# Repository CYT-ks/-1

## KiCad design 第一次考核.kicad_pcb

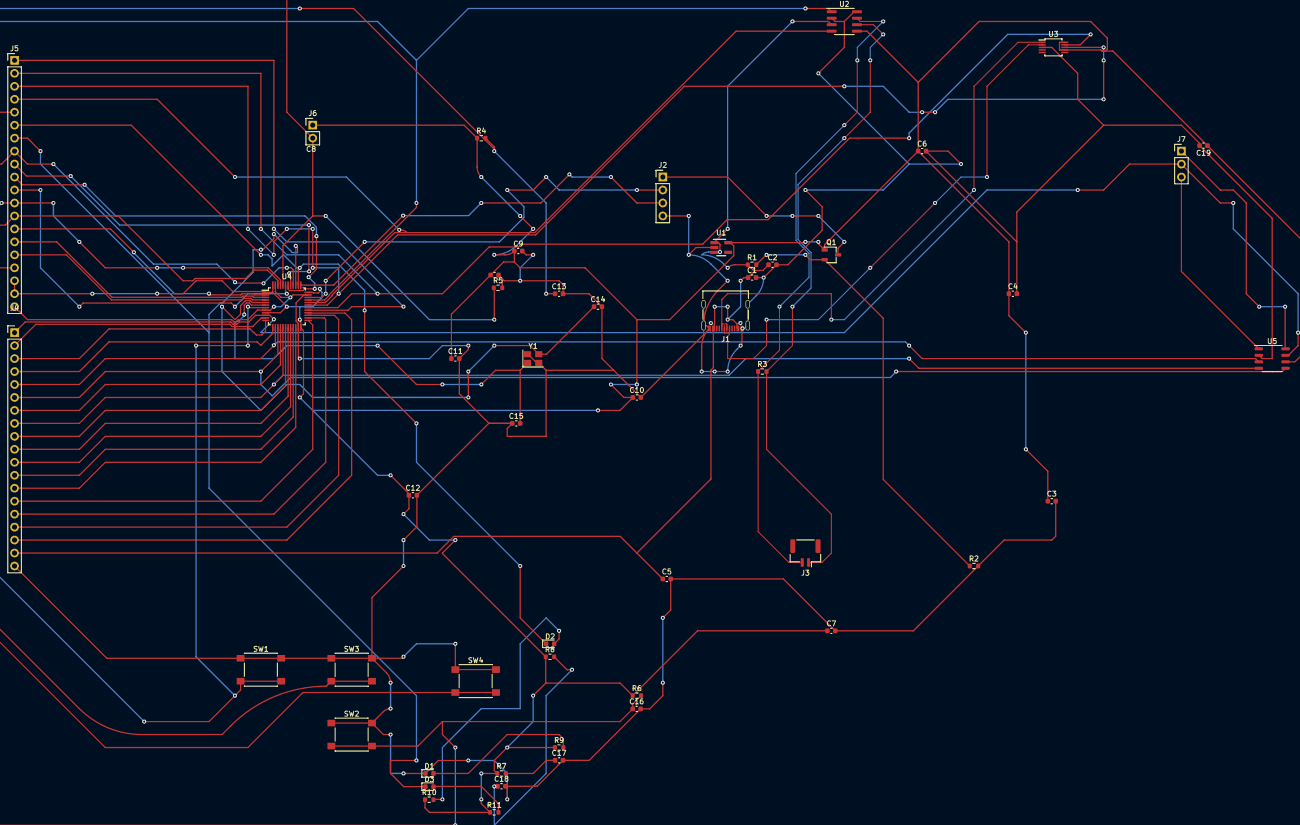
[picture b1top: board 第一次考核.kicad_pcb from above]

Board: 2 copper layers, 51 parts (0 on the bottom side), 55 nets.

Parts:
C1, C3: 10u; C_0603_1608Metric
C2, C4, C5, C6, C7, C8, C9, C10, C11, C12, C13, C16, C17, C18, C19: 100n; C_0603_1608Metric
C14, C15: 18p; C_0603_1608Metric
D1, D2, D3: LED; LED_0603_1608Metric
J1: USB_C_Receptacle_USB2.0; USB_C_Receptacle_Palconn_UTC16-G
J2: PinHeader_1x04_P2.54mm_Vertical
J3: Conn_01x02; JST_GH_SM02B-GHS-TB_1x02-1MP_P1.25mm_Horizontal
J4: Conn_01x19; PinHeader_1x19_P2.54mm_Vertical
J5: Conn_01x20; PinHeader_1x20_P2.54mm_Vertical
J6: Conn_01x02; PinHeader_1x02_P2.54mm_Vertical
J7: Conn_01x03; PinHeader_1x03_P2.54mm_Vertical
Q1: TSOT-23
R1: 1k; R_0603_1608Metric
R2, R4, R5: 10k; R_0603_1608Metric
R3: 120; R_0603_1608Metric
R6, R7, R8: 1K; R_0603_1608Metric
R9, R10, R11: R; R_0603_1608Metric
SW1, SW2, SW3, SW4: SW_Push; SW_Push_1P1T_NO_6x6mm_H9.5mm
U1: HX9193; SOT-23-5_HandSoldering
U2: TJA1051T-3; SOIC-8_3.9x4.9mm_P1.27mm
U3: CH340E; MSOP-10_3x3mm_P0.5mm
U4: STM32F103C8T6; LQFP-48_7x7mm_P0.5mm
U5: AD8400ARZ50; SOP-8_3.9x4.9mm_P1.27mm
Y1: 12M; Crystal_SMD_3225-4Pin_3.2x2.5mm

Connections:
+3V3: C3.1, C4.1, C6.1, C7.1, C8.1, C9.1, C10.1, C11.1, C12.1, C19.1, J5.18, J5.19, J6.1, Q1.1 (D), R4.1, R6.1, R7.1, R8.1, R9.1, R10.1, R11.1, U1.5 (VOUT), U2.5 (VIO), U3.7 (VCC), U3.10 (V3), U4.1 (VBAT), U4.9 (VDDA), U4.24 (VDD), U4.36 (VDD), U4.48 (VDD), U5.6 (VDD)
/PORT&POWER/3V3_Debug: J2.1, Q1.3 (S)
/PORT&POWER/CAN+: J3.2, R3.1, U2.7 (CANH)
/PORT&POWER/CAN-: J3.1, R3.2, U2.6 (CANL)
/PORT&POWER/D+: J1.A6 (D+), J1.B6 (D+), U3.1 (UD+)
/PORT&POWER/D-: J1.A7 (D-), J1.B7 (D-), U3.2 (UD-)
/STM32_MinimumSystem/BOOTO: J5.17, J6.2, R5.1, U4.44 (BOOT0)
/STM32_MinimumSystem/NRST: C13.1, R4.2, SW1.2, U4.7 (NRST)
/STM32_MinimumSystem/OSC_IN: C14.1, U4.5 (PD0), Y1.3
/STM32_MinimumSystem/OSC_OUT: C15.2, U4.6 (PD1), Y1.1
/STM32_MinimumSystem/PA0: J4.1, J7.2, U4.10 (PA0), U5.7 (W1)
/STM32_MinimumSystem/PA1: J4.2, U4.11 (PA1)
/STM32_MinimumSystem/PA2: J4.3, U4.12 (PA2)
/STM32_MinimumSystem/PA3: J4.4, U4.13 (PA3)
/STM32_MinimumSystem/PA4: J4.5, U4.14 (PA4), U5.3 (~CS)
/STM32_MinimumSystem/PA5: J4.6, U4.15 (PA5), U5.5 (CLK)
/STM32_MinimumSystem/PA6: J4.7, U4.16 (PA6)
/STM32_MinimumSystem/PA7: J4.8, U4.17 (PA7), U5.4 (SDI)
/STM32_MinimumSystem/PA8: J5.1, U4.29 (PA8)
/STM32_MinimumSystem/PA9: J5.2, U3.9 (RXD), U4.30 (PA9)
/STM32_MinimumSystem/PA10: J5.3, U3.8 (TXD), U4.31 (PA10)
/STM32_MinimumSystem/PA11: J5.4, U2.4 (RXD), U4.32 (PA11)
/STM32_MinimumSystem/PA12: J5.5, U2.1 (TXD), U4.33 (PA12)
/STM32_MinimumSystem/PA13: J2.2, U4.34 (PA13)
/STM32_MinimumSystem/PA14: J2.3, U4.37 (PA14)
/STM32_MinimumSystem/PA15: D2.1 (K), J5.6, U4.38 (PA15)
/STM32_MinimumSystem/PB0: J4.9, U4.18 (PB0)
/STM32_MinimumSystem/PB1: J4.10, U4.19 (PB1)
/STM32_MinimumSystem/PB2: J4.11, U4.20 (PB2)
/STM32_MinimumSystem/PB3: D3.1 (K), J5.7, U4.39 (PB3)
/STM32_MinimumSystem/PB4: C16.1, J5.8, R6.2, SW2.2, U4.40 (PB4)
/STM32_MinimumSystem/PB5: J5.9, U4.41 (PB5)
/STM32_MinimumSystem/PB6: J5.10, U4.42 (PB6)
/STM32_MinimumSystem/PB7: J5.11, U4.43 (PB7)
/STM32_MinimumSystem/PB8: J5.12, SW3.2, U4.45 (PB8)
/STM32_MinimumSystem/PB9: J5.13, SW4.2, U4.46 (PB9)
/STM32_MinimumSystem/PB10: J4.12, U4.21 (PB10)
/STM32_MinimumSystem/PB11: J4.13, U4.22 (PB11)
/STM32_MinimumSystem/PB12: J4.14, U4.25 (PB12)
/STM32_MinimumSystem/PB13: J4.15, U4.26 (PB13)
/STM32_MinimumSystem/PB14: J4.16, U4.27 (PB14)
/STM32_MinimumSystem/PB15: J4.17, U4.28 (PB15)
/STM32_MinimumSystem/PC13: J5.14, U4.2 (PC13)
/STM32_MinimumSystem/PC14: J5.15, U4.3 (PC14)
/STM32_MinimumSystem/PC15: J5.16, U4.4 (PC15)
GND: C1.2, C2.2, C3.2, C4.2, C5.2, C6.2, C7.2, C8.2, C9.2, C10.2, C11.2, C12.2, C13.2, C14.2, C15.1, C16.2, C17.2, C18.2, C19.2, D1.1 (K), J1.A1 (GND), J1.A12 (GND), J1.B1 (GND), J1.B12 (GND), J1.S1 (SHIELD), J2.4, J4.19, J5.20, R2.2, R5.2, SW1.1, SW2.1, SW3.1, SW4.1, U1.2 (GND), U2.2 (GND), U2.8 (S), U3.3 (GND), U4.8 (VSSA), U4.23 (VSS), U4.35 (VSS), U4.47 (VSS), U5.2 (GND), Y1.2, Y1.4
unnamed: C17.1, R7.2
unnamed: C18.1, R8.2
unnamed: D1.2 (A), R9.2
unnamed: D2.2 (A), R10.2
unnamed: D3.2 (A), R11.2
unnamed: J7.1, U5.8 (A1)
unnamed: J7.3, U5.1 (B1)
unnamed: Q1.2 (G), R1.2, R2.1
VBUS: C1.1, C2.1, C5.1, J1.A4 (VBUS), J1.A9 (VBUS), J1.B4 (VBUS), J1.B9 (VBUS), J4.18, R1.1, U1.1 (VIN), U1.3 (EN), U2.3 (VCC)

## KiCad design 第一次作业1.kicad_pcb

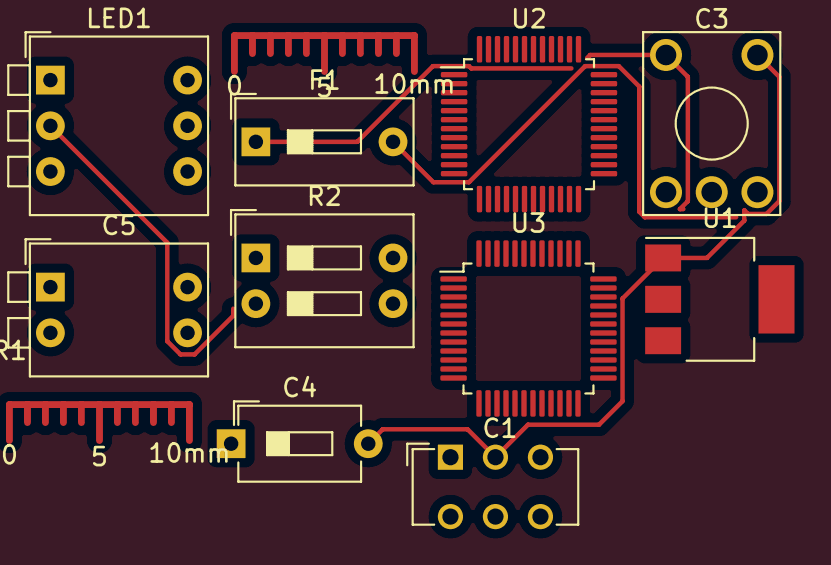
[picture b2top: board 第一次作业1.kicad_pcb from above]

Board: 2 copper layers, 12 parts (0 on the bottom side), 5 nets.

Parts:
C1: 104/10V; SW_CuK_JS202011CQN_DPDT_Straight
C2: 470UF/10V; Gauge_10mm_Type1_CopperTop
C3: 104/10V; KSA_Tactile_SPST
C4: 104/10V; SW_DIP_SPSTx01_Slide_6.7x4.1mm_W7.62mm_P2.54mm_LowProfile
C5: 470UF/10V; SW_DIP_SPSTx02_Piano_CTS_Series194-2MSTN_W7.62mm_P2.54mm
F1: 6.5V/0.2A; SW_DIP_SPSTx01_Slide_9.78x4.72mm_W7.62mm_P2.54mm
LED1: LED; SW_DIP_SPSTx03_Piano_CTS_Series194-3MSTN_W7.62mm_P2.54mm
R1: R; Gauge_10mm_Type1_CopperTop
R2: R; SW_DIP_SPSTx02_Slide_9.78x7.26mm_W7.62mm_P2.54mm
U1: AP1117-33; SOT-223-3_TabPin2
U2, U3: STM32F030C8Tx; LQFP-48_7x7mm_P0.5mm

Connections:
+3.3V: R2.1, U2.1 (VDD), U2.9 (VDDA), U2.24 (VDD), U2.48 (VDD), U3.1 (VDD), U3.9 (VDDA), U3.24 (VDD), U3.48 (VDD)
/RST: C1.1, R2.2, U2.7 (NRST), U3.7 (NRST)
GND: C1.2, C3.2, C4.2, C5.2, LED1.1 (K), U1.1 (GND), U2.8 (VSSA), U2.23 (VSS), U2.47 (VSS), U3.8 (VSSA), U3.23 (VSS), U3.47 (VSS)
unnamed: C3.1, F1.1, U1.3 (VI)
unnamed: C4.1, C5.1, U1.2 (VO)

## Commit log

2022-10-06 Create 第一次考核1
2022-10-07 作业提交
